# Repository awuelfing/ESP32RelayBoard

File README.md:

# ESP32RelayBoard
KiCad and Gerber files, and code, for a PCB using an ESP32 dev board and UDN2981A drivers to run 16 relays.  High-side switching.

Currently both the PCB and code are untested.

Intended for use with

EzSBC ESP32_SW High Supply Voltage Breakout and Development Board
https://www.ezsbc.com/product/wifi01-sw/

as well as 2x UDN2981A
https://media.digikey.com/pdf/Data%20Sheets/Allegro%20PDFs/2981_2982_Rev2012.pdf

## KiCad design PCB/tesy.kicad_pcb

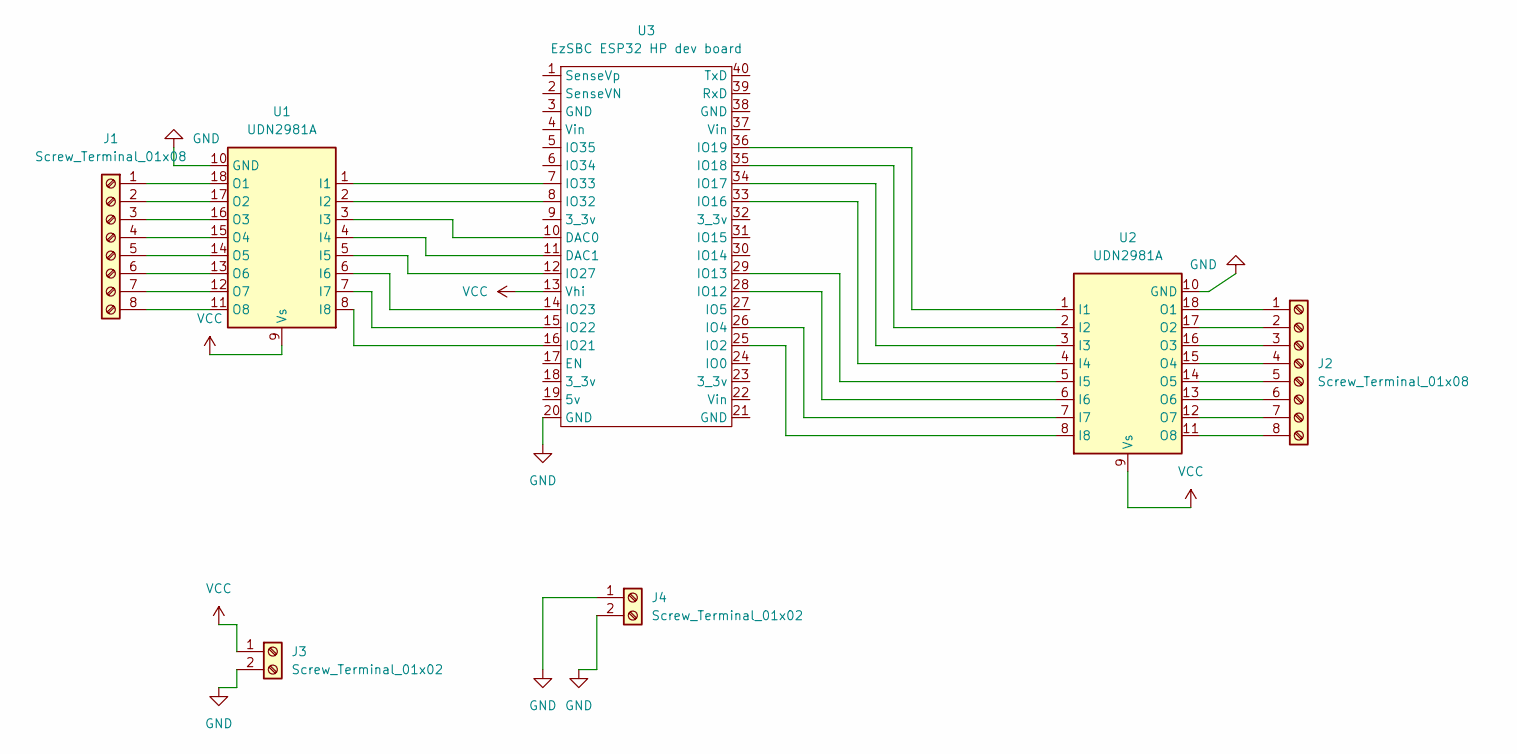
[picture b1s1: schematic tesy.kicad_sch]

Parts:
J1, J2: Screw_Terminal_01x08; Term_Block_1x8_P5.08mm
J3, J4: Screw_Terminal_01x02; PinHeader_1x02_P2.54mm_Vertical
U1, U2: UDN2981A; DIP-18_W7.62mm
U3: EzSBC ESP32 HP dev board; 40pin 9row

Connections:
GND: J3.2, J4.1, J4.2, U1.10 (GND), U2.10 (GND), U3.20 (GND)
unnamed: J1.1, U1.18 (O1)
unnamed: J1.2, U1.17 (O2)
unnamed: J1.3, U1.16 (O3)
unnamed: J1.4, U1.15 (O4)
unnamed: J1.5, U1.14 (O5)
unnamed: J1.6, U1.13 (O6)
unnamed: J1.7, U1.12 (O7)
unnamed: J1.8, U1.11 (O8)
unnamed: J2.1, U2.18 (O1)
unnamed: J2.2, U2.17 (O2)
unnamed: J2.3, U2.16 (O3)
unnamed: J2.4, U2.15 (O4)
unnamed: J2.5, U2.14 (O5)
unnamed: J2.6, U2.13 (O6)
unnamed: J2.7, U2.12 (O7)
unnamed: J2.8, U2.11 (O8)
unnamed: U1.1 (I1), U3.7 (IO33)
unnamed: U1.2 (I2), U3.8 (IO32)
unnamed: U1.3 (I3), U3.10 (DAC0)
unnamed: U1.4 (I4), U3.11 (DAC1)
unnamed: U1.5 (I5), U3.12 (IO27)
unnamed: U1.6 (I6), U3.14 (IO23)
unnamed: U1.7 (I7), U3.15 (IO22)
unnamed: U1.8 (I8), U3.16 (IO21)
unnamed: U2.1 (I1), U3.36 (IO19)
unnamed: U2.2 (I2), U3.35 (IO18)
unnamed: U2.3 (I3), U3.34 (IO17)
unnamed: U2.4 (I4), U3.33 (IO16)
unnamed: U2.5 (I5), U3.29 (IO13)
unnamed: U2.6 (I6), U3.28 (IO12)
unnamed: U2.7 (I7), U3.26 (IO4)
unnamed: U2.8 (I8), U3.25 (IO2)
VCC: J3.1, U1.9 (Vs), U2.9 (Vs), U3.13 (Vhi)

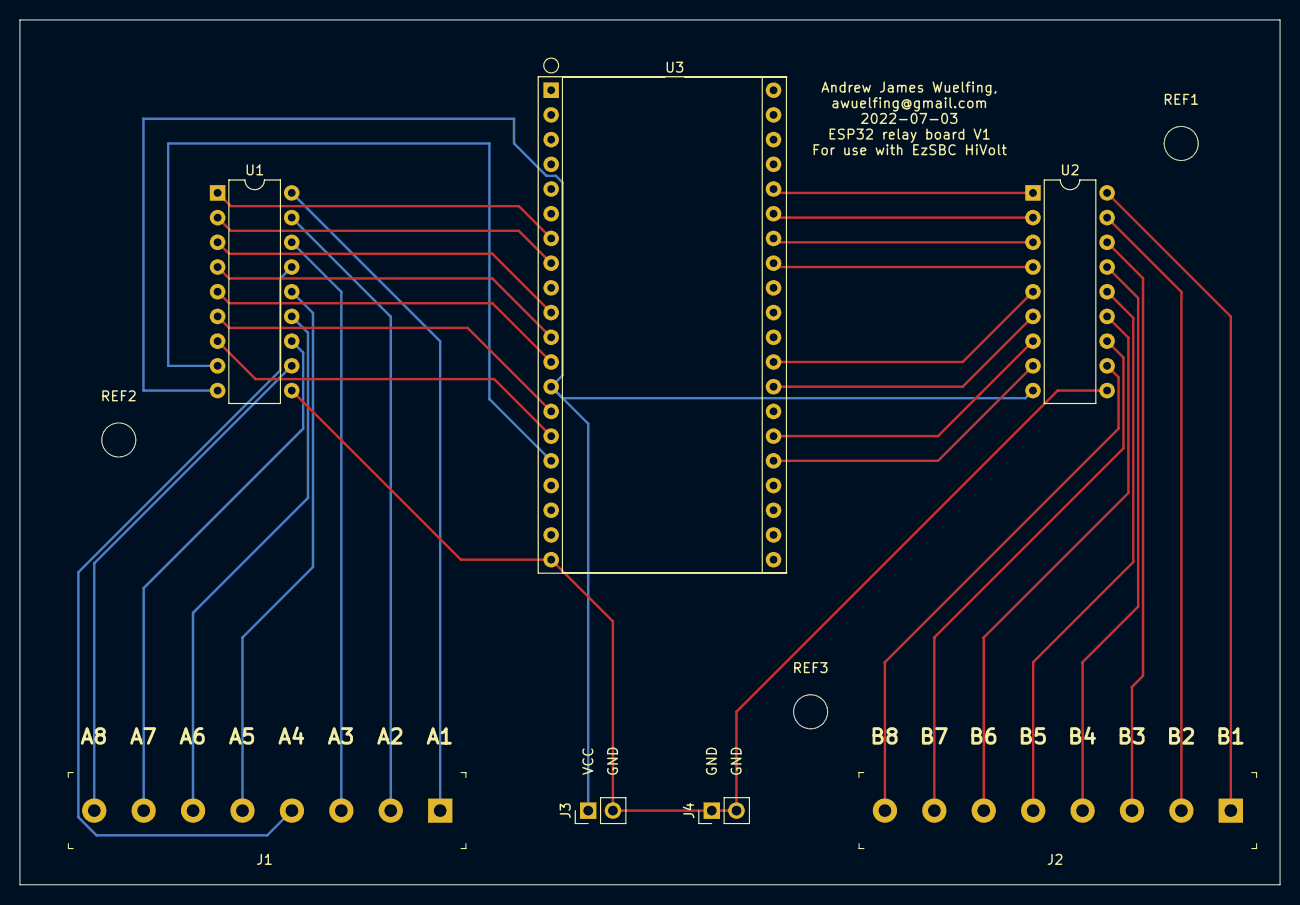
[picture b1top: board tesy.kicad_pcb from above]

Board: 2 copper layers, 129.5 x 88.9 mm, 10 parts (0 on the bottom side), 34 nets.

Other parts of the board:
REF1, REF2, REF3: MountingHole_3.5mm

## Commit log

2022-07-04 add PCB files
2022-07-04 add code based on a previous attempt at this. removed the current sensing and temp sensor
2022-07-04 added password to gitignore
2022-07-04 brought over missing #define
